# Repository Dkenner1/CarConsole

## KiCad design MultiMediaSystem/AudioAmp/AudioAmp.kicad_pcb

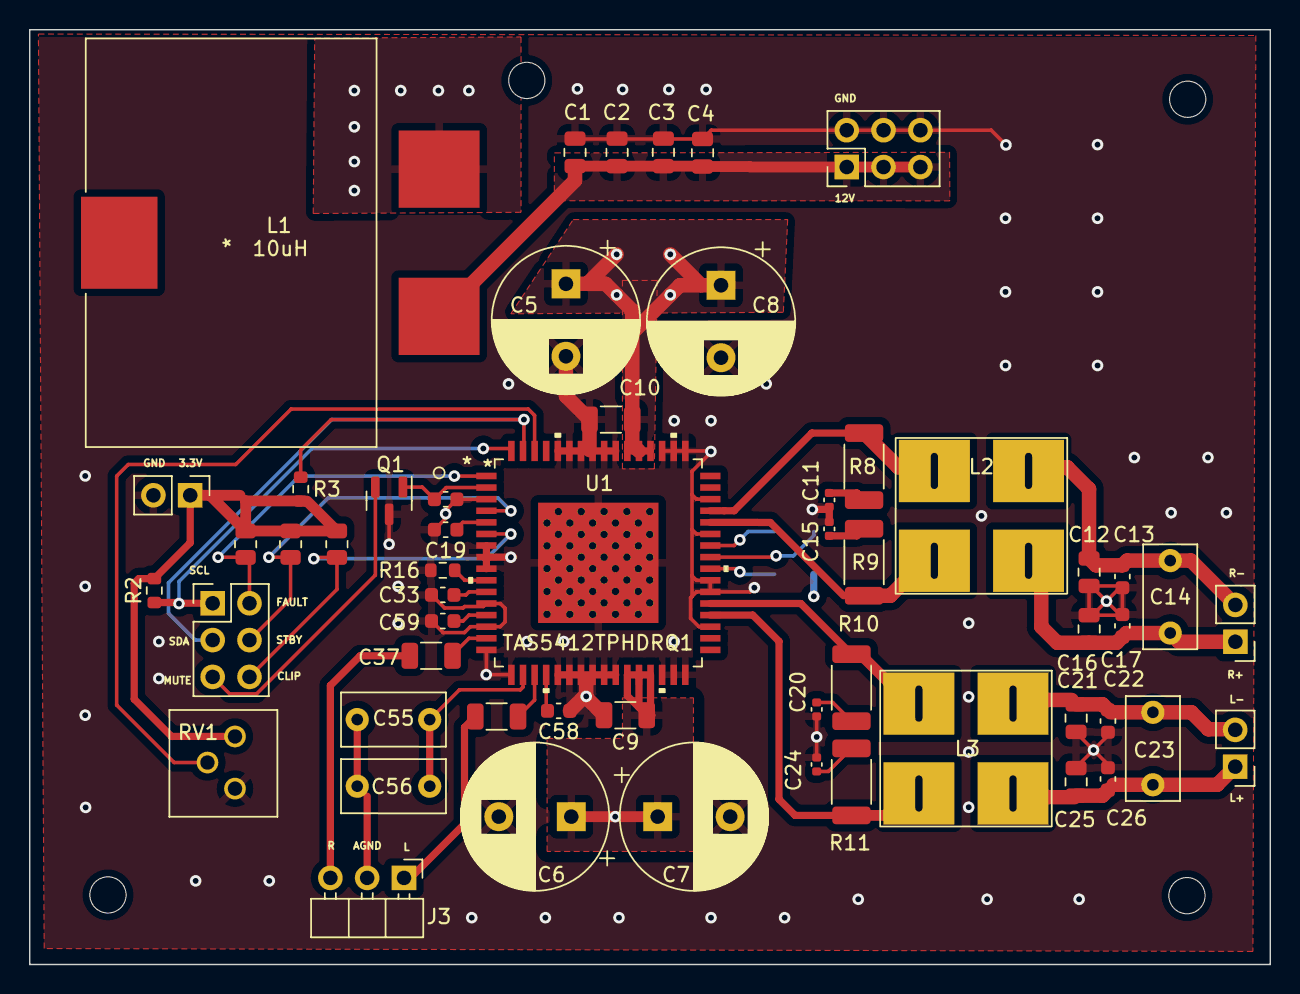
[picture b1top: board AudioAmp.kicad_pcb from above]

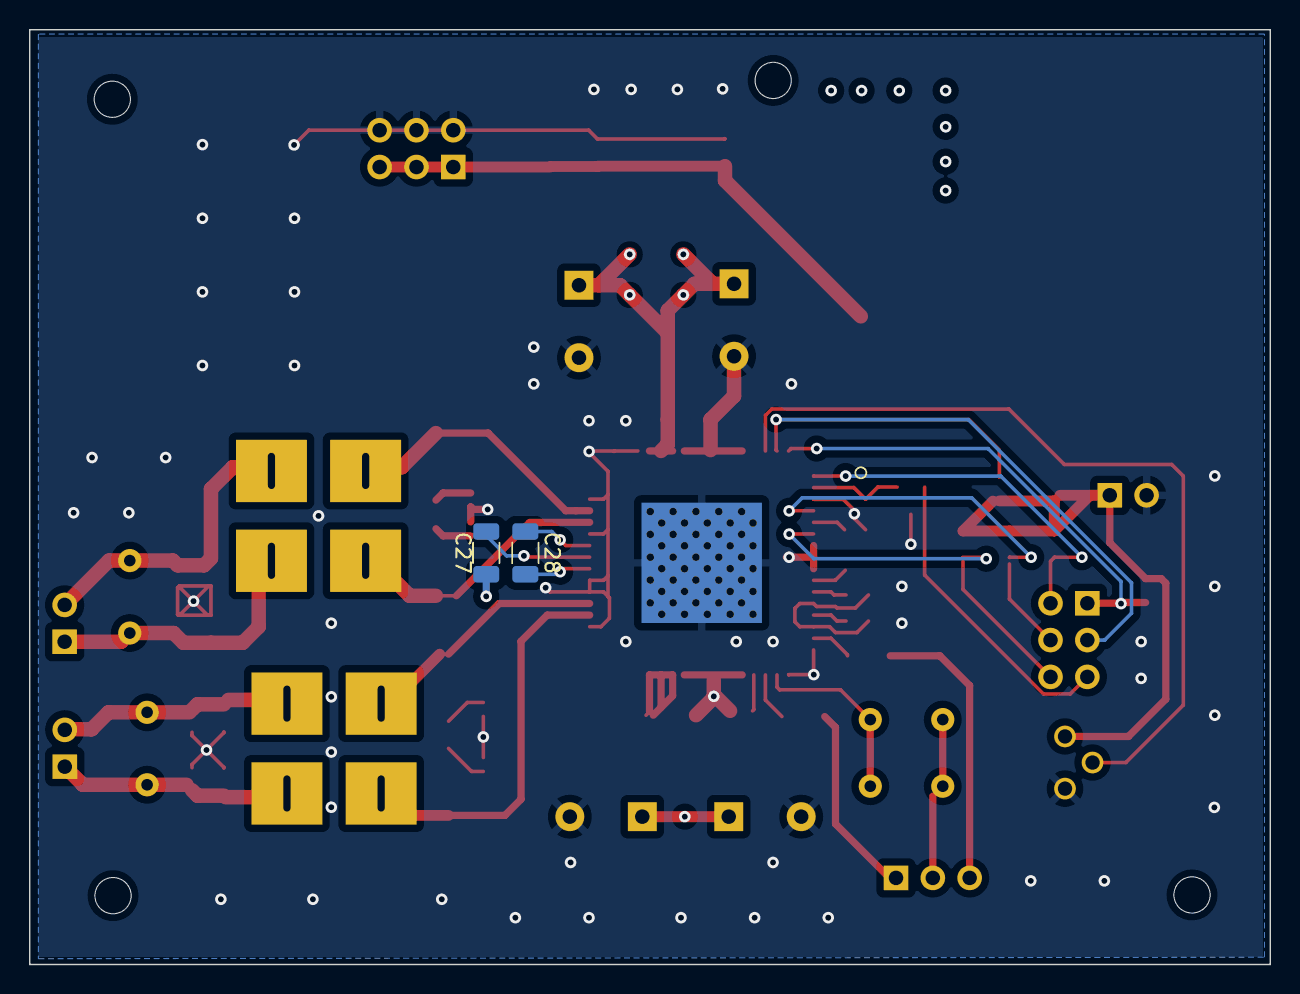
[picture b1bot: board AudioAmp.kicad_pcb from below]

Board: 4 copper layers, 85.6 x 64.5 mm, 61 parts (2 on the bottom side), 38 nets.

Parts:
C1, C2: 4.7uF; C_0805_2012Metric
C3: 82nF; C_0805_2012Metric
C4: 2.2nF; C_0805_2012Metric
C5, C6, C7, C8: 330uF; CP_Radial_D10.0mm_P5.00mm
C9, C10, C27, C28: 1uF; C_1206_3216Metric
C11, C15, C20, C24: 1nF; C_0402_1005Metric
C12, C16, C21, C25: 470nF; C_0805_2012Metric
C13, C17, C22, C26: 10nF; C_0603_1608Metric
C14, C23, C55, C56: .47uF; C_Rect_L7.0mm_W3.5mm_P5.00mm
C18: 220nF; C_0603_1608Metric
C19, C33, C58, C59: 100nF; C_0603_1608Metric
C37, C39: .47uF; C_1206_3216Metric
H1, H2, H3, H4: MountingHole; MountingHole_2.5mm
J1: Ctrl_pins; PinHeader_2x03_P2.54mm_Vertical
J2: PWR; PinHeader_2x03_P2.54mm_Vertical
J3: AudioIn; PinHeader_1x03_P2.54mm_Horizontal
J4: PULLUP_SRC; PinHeader_1x02_P2.54mm_Vertical
J5: Rspkr_o; PinHeader_1x02_P2.54mm_Vertical
J6: Lspkr_o; PinHeader_1x02_P2.54mm_Vertical
L1: 10uH; SER2918H-103KL
L2, L3: 10uH; JA4575-AL
Q1: q; SOT-23
R2, R3: 4.7K; R_0603_1608Metric
R5, R6, R7: 49.9K; R_0805_2012Metric
R8, R9, R10, R11: 5.6; R_2010_5025Metric
R16: 20k; R_0603_1608Metric
RV1: 50K pot; CT-6EW
U1: TAS5412TPHDRQ1

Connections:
+3V3: J4.1, R2.2, R3.2, R5.2, R6.2, R7.2, RV1.1
+12V: C1.1, C2.1, C3.1, C4.1, J2.1, J2.3, J2.5, L1.1
AudioGND: C55.1, C56.1, J3.2
CLIP_OTW: J1.6, R7.1, U1.6 (*CLIP_OTW)
CP: C27.2, U1.41 (CP)
CPC_TOP: C28.1, U1.42 (CPC_TOP)
CP_BOT: C28.2, U1.40 (CP_BOT)
FAULT: J1.2, R5.1, U1.1 (*FAULT)
GND: C1.2, C2.2, C3.2, C4.2, C5.2, C6.2, C7.2, C8.2, C9.2, C10.2, C11.1, C12.1, C13.1, C15.2, C16.2, C17.2, C18.2, C19.2, C20.1, C21.1, C22.1, C24.2, C25.2, C26.2, C33.2, C58.1, C59.2, J2.2, J2.4, J2.6, J4.2, Q1.3 (S), R16.1, RV1.3, U1.3 (GND), U1.7 (GND), U1.8 (GND), U1.9 (GND), U1.12 (GND), U1.14 (GND), U1.16 (GND), U1.17 (GND), U1.21 (GND), U1.22 (GND), U1.23 (GND), U1.24 (GND), U1.25 (GND), U1.26 (GND), U1.30 (GND), U1.31 (GND), U1.32 (GND), U1.35 (GND), U1.38 (GND), U1.39 (GND), U1.43 (GND), U1.46 (GND), U1.49 (GND), U1.50 (GND), U1.51 (GND), U1.55 (GND), U1.56 (GND), U1.57 (GND), U1.58 (GND), U1.59 (GND), U1.60 (GND), U1.EPAD
I2C_ADDR: RV1.2, U1.62 (I2C_ADDR)
IN1_P: C37.2, U1.15 (IN1_P)
IN2_P: C39.2, U1.19 (IN2_P)
IN_M: C55.2, C56.2, U1.18 (IN_M)
L: C39.1, J3.1
L_o+: C23.2, C25.1, C26.1, J6.1, L3.3
L_o-: C21.2, C22.2, C23.1, J6.2, L3.2
MUTE: J1.5, Q1.2 (G)
MUTE*: C18.1, Q1.1 (D), U1.2 (*MUTE)
unnamed: C11.2, R8.2
unnamed: C15.1, R9.1
unnamed: C19.1, U1.5 (D_BYP)
unnamed: C20.2, R10.2
unnamed: C24.1, R11.1
unnamed: C33.1, U1.11 (A_BYP)
unnamed: C58.2, U1.20 (CM_CAP2)
unnamed: C59.1, U1.13 (CM_CAP1)
unnamed: R16.2, U1.10 (REXT)
OUT1_M: L2.1, R8.1, U1.45 (OUT1_M)
OUT1_P: L2.4, R9.2, U1.44 (OUT1_P)
OUT2_M: L3.1, R10.1, U1.37 (OUT2_M)
OUT2_P: L3.4, R11.2, U1.36 (OUT2_P)
PVDD: C5.1, C6.1, C7.1, C8.1, C9.1, C10.1, C27.1, L1.2, U1.27 (PVDD), U1.28 (PVDD), U1.29 (PVDD), U1.52 (PVDD), U1.53 (PVDD), U1.54 (PVDD)
R: C37.1, J3.3
R_o+: C14.2, C16.1, C17.1, J5.1, L2.3
R_o-: C12.2, C13.2, C14.1, J5.2, L2.2
SCL: J1.1, R2.1, U1.64 (SCL)
SDA: J1.3, R3.1, U1.63 (SDA)
STANDBY: J1.4, R6.1, U1.4 (*STANDBY)

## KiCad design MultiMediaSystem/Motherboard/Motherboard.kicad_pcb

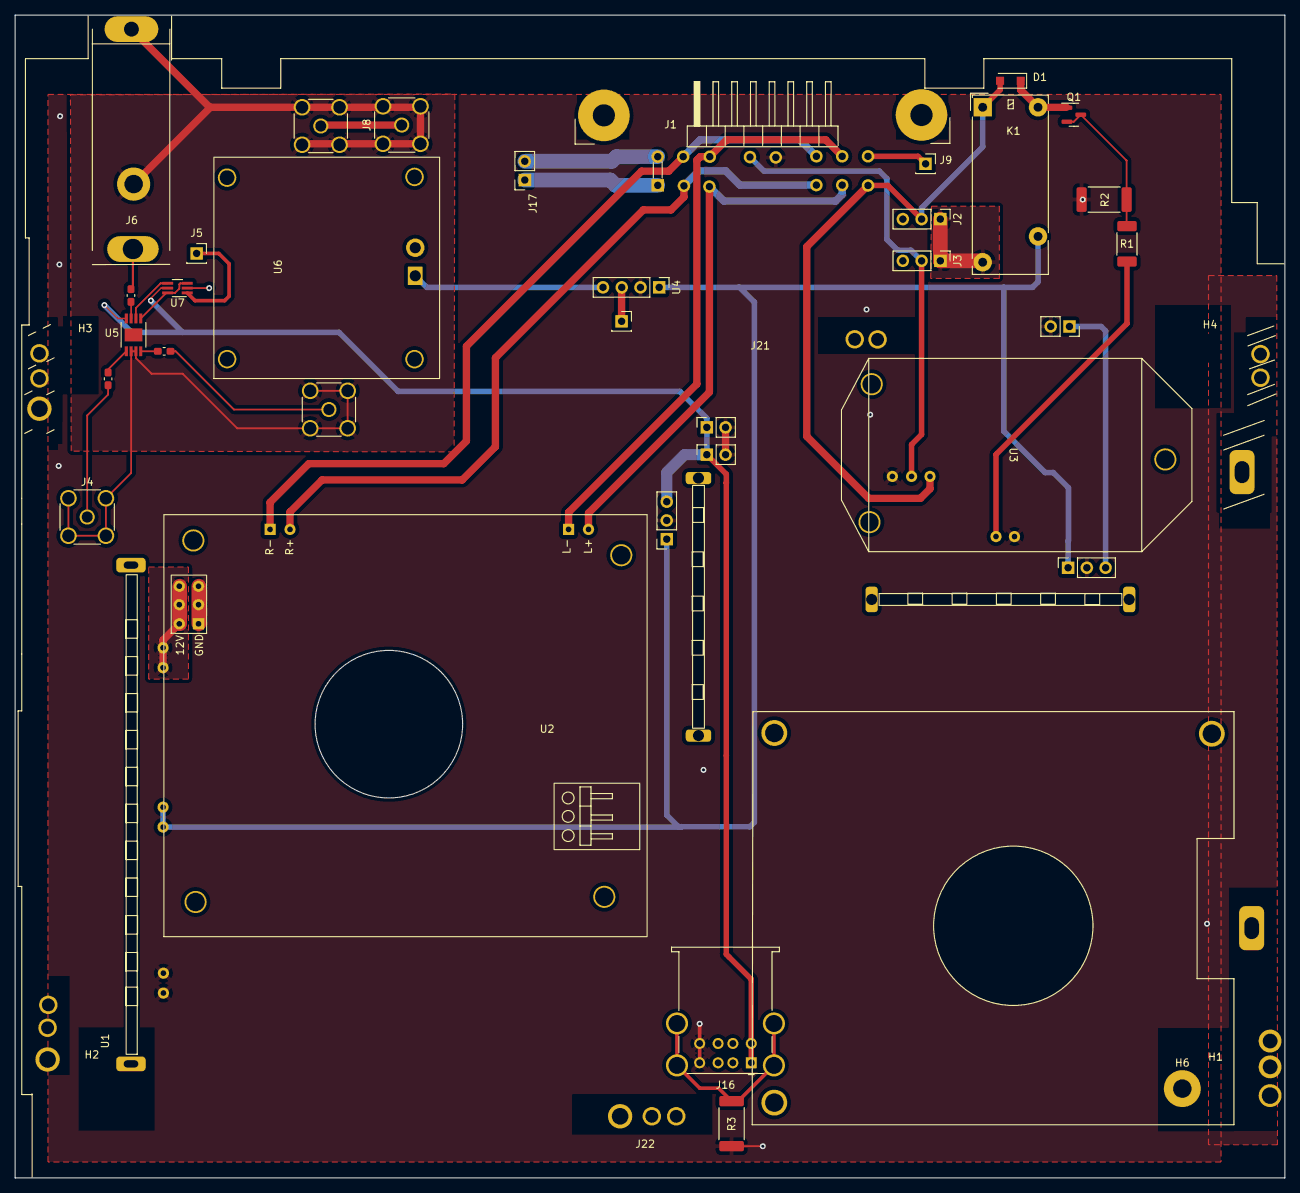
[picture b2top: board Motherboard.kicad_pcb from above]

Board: 2 copper layers, 172.1 x 157.6 mm, 42 parts (0 on the bottom side), 32 nets.

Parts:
C1, C2, C3: 10uF; C_0603_1608Metric_Pad1.08x0.95mm_HandSolder
D1: FS1B; D_SOD-123F
H1, H2, H3, H4: MountingHole; RectangleSlot
H5, H6, H7, H8: DAC_mount; MountingHole_2.5mm_Pad
J1: Wire Harness; HeadUnit_Conn
J2: Vmem Jumper; PinHeader_1x03_P2.54mm_Vertical
J3: Vacc_jumper; PinHeader_1x03_P2.54mm_Vertical
J4: RF_RX; SMA_Amphenol_132134_Vertical
J5: RF_CTRL; PinSocket_1x01_P2.54mm_Vertical
J6: AntennaExternal; SubaruRadioJack
J8: RF_TX; SMA_Amphenol_132134_Vertical
J9: AntennaPwr_Conn; PinSocket_1x01_P2.54mm_Vertical
J10: RF_EN; PinSocket_1x01_P2.54mm_Vertical
J14: 5V_1; PinSocket_1x02_P2.54mm_Vertical
J15: RPI_Buck; 5V_Reg_Footprint_VertMnt
J16: AUSB2-4599; USB_A_Wuerth_61400826021_Horizontal_Stacked
J17: Illum/Dim; PinSocket_1x02_P2.54mm_Vertical
J18: 5V_2; PinSocket_1x02_P2.54mm_Vertical
J19: GP_Buck; 5V_Reg_Footprint_VertMnt
J20: 5V_3; PinSocket_1x02_P2.54mm_Vertical
J21: Motherboard bracket; MotherBoard_Bracket_2
J22: Motherboard bracket; MotherBoard_Bracket_1
K1: ADW1112HTW; Relay_1P1T_NO_10x24x18.8mm_Panasonic_ADW11xxxxW_THT
Q1: T2N7002BK,LM; SOT-23
R1: RMCP2010FT470R; R_2010_5025Metric_Pad1.40x2.65mm_HandSolder
R2: RC2512JK-0747KL; R_2512_6332Metric_Pad1.40x3.35mm_HandSolder
R3: HCJ2512ZT0R00; R_2512_6332Metric_Pad1.40x3.35mm_HandSolder
U1: AudioAmp_PS
U2: AudioAmp
U3: PowerSupplyCtrl; PS_Controller
U4: RadioRegulator; PinHeader_1x04_P2.54mm_Vertical
U5: HMC784AMS8GETR
U6: RadioAmp
U7: SN74LVC2G06QDCKRQ1; SOT-363_SC-70-6_Handsoldering

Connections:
5V: J14.1, J15.3
5V_GP: J16.1 (VBUS1), J16.5 (VBUS2), J18.1, J19.3, J20.1, U5.4 (VDD), U7.5 (VCC)
8V: U4.4 (Vradio), U6.1 (Vsrc)
Antenna: C1.1, J6.1 (In)
Antenna_Pwr: J1.14, J9.1
AudioPwr: U1.3 (Vout), U2.1 (12V)
Dim: J1.7, J17.2
FrontSpkr_L+: J1.3, J1.5, U2.5 (L+)
FrontSpkr_L-: J1.9, J1.13, U2.6 (L-)
FrontSpkr_R+: J1.2, J1.4, U2.3 (R+)
FrontSpkr_R-: J1.8, J1.12, U2.4 (R-)
GND: J1.11, J14.2, J15.2, J16.4 (GND1), J16.8 (GND2), J18.2, J19.2, J20.2, R2.1, R3.1, U1.2 (GND), U2.2 (GND), U3.3 (GND), U4.2 (GND), U6.2 (GND), U7.2 (GND)
Illum: J1.1, J17.1
unnamed: C1.2, U5.3 (RFC)
unnamed: C2.1, U5.5 (RF1)
unnamed: C3.1, U5.8 (RF2)
unnamed: D1.1 (K), K1.6, Q1.1 (D)
unnamed: J16.9 (Shield), R3.2
unnamed: Q1.2 (G), Q1.3 (S), R1.2, R2.2
RELAY: R1.1, U3.6 (SWITCH)
RF_A: U5.1 (A), U7.3 (2A), U7.6 (1Y)
RF_ATX: C3.2, U6.5 (out)
RF_B: U5.2 (B), U7.4 (2Y)
RF_CTL: J5.1, U7.1 (1A)
RF_RX: C2.2, J4.1 (In)
RF_TX: J8.1 (In), U6.3 (in)
RF_gnd: J4.2 (Ext), J6.2 (Ext), J8.2 (Ext), U5.6 (GND), U5.7 (GND), U6.4 (in_gnd), U6.6 (out_gnd)
Radio_EN: J10.1, U4.3 (EN)
Vacc: J1.10, J3.2, U3.2 (Vmes)
Vdd: J2.1, J3.1, K1.3
Vmem: D1.2 (A), J1.6, J2.2, K1.1, U3.1 (Vin)
Vsrc: J15.1, J19.1, K1.5, U1.1 (Vin), U4.1 (Vsrc)

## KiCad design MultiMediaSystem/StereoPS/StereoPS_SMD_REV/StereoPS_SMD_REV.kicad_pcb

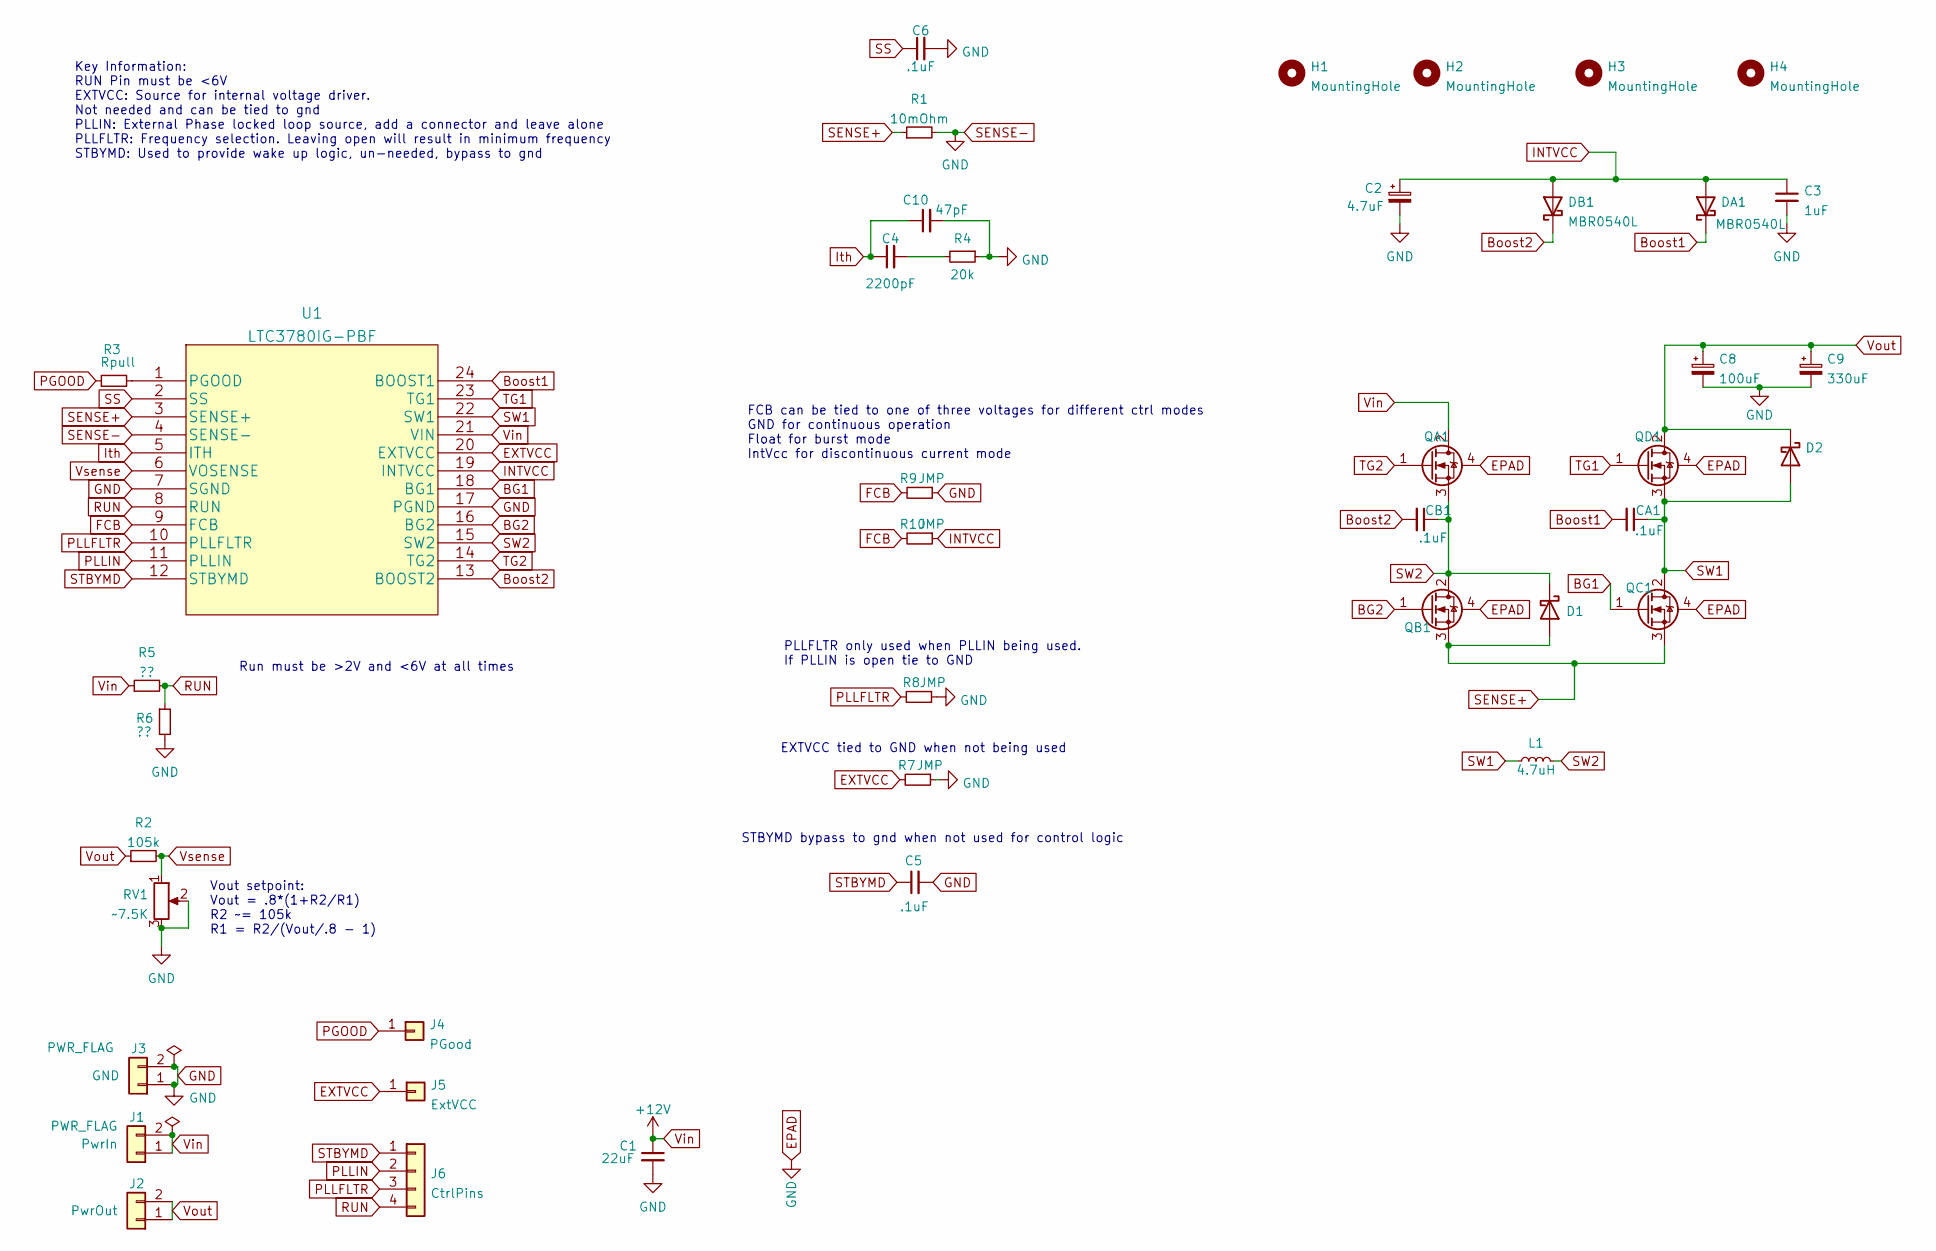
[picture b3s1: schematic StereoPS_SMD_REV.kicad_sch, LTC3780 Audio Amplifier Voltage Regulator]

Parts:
C1: 22uF; C_1206_3216Metric_Pad1.33x1.80mm_HandSolder
C2: 4.7uF; C_0805_2012Metric_Pad1.18x1.45mm_HandSolder
C3: 1uF; C_1206_3216Metric_Pad1.33x1.80mm_HandSolder
C4: 2200pF; C_0805_2012Metric_Pad1.18x1.45mm_HandSolder
C5, C6: .1uF; C_0603_1608Metric_Pad1.08x0.95mm_HandSolder
C8: 100uF; CP_Radial_D8.0mm_P3.50mm
C9: 330uF; CP_Radial_D10.0mm_P5.00mm
C10: 47pF; C_0603_1608Metric_Pad1.08x0.95mm_HandSolder
CA1: .1uF; C_0603_1608Metric_Pad1.08x0.95mm_HandSolder
CB1: .1uF; C_0603_1608Metric_Pad1.08x0.95mm_HandSolder
D1: SS34-E3; D_SOD-123
D2: SS32-E3; D_SOD-123
DA1: MBR0540L; D_SOD-123
DB1: MBR0540L; D_SOD-123
H1, H2, H3, H4: MountingHole; MountingHole_2.5mm
J1: PwrIn; PinHeader_1x02_P2.54mm_Horizontal
J2: PwrOut; PinHeader_1x02_P2.54mm_Horizontal
J3: GND; PinHeader_1x02_P2.54mm_Horizontal
J4: PGood; PinSocket_1x01_P2.54mm_Vertical
J5: ExtVCC; PinSocket_1x01_P2.54mm_Vertical
J6: CtrlPins; PinSocket_1x04_P2.54mm_Vertical
L1: 4.7uH; L_12x12mm_H8mm
QA1: RX3G07CGNC16; MSOP-8-1EP_3x3mm_P0.65mm_EP1.73x1.85mm
QB1: RX3G07CGNC16; MSOP-8-1EP_3x3mm_P0.65mm_EP1.73x1.85mm
QC1: RX3G07CGNC16; MSOP-8-1EP_3x3mm_P0.65mm_EP1.73x1.85mm
QD1: RX3G07CGNC16; MSOP-8-1EP_3x3mm_P0.65mm_EP1.73x1.85mm
R1: 10mOhm; R_0402_1005Metric_Pad0.72x0.64mm_HandSolder
R2: 105k; R_1206_3216Metric_Pad1.30x1.75mm_HandSolder
R3: Rpull; R_0805_2012Metric_Pad1.20x1.40mm_HandSolder
R4: 20k; R_1206_3216Metric_Pad1.30x1.75mm_HandSolder
R5, R6: ??; R_0805_2012Metric_Pad1.20x1.40mm_HandSolder
R7, R8, R9, R10: JMP; R_0805_2012Metric_Pad1.20x1.40mm_HandSolder
RV1: ~7.5K; CT-6EW
U1: LTC3780IG-PBF

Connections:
BG1: QC1.1 (G), U1.18 (BG1)
BG2: QB1.1 (G), U1.16 (BG2)
Boost1: CA1.2, DA1.1 (K), U1.24 (BOOST1)
Boost2: CB1.2, DB1.1 (K), U1.13 (BOOST2)
EPAD: C1.2, C2.2, C3.2, C5.2, C6.2, C8.2, C9.2, C10.2, J3.1, J3.2, QA1.4 (EPAD), QB1.4 (EPAD), QC1.4 (EPAD), QD1.4 (EPAD), R1.2, R4.1, R6.2, R7.1, R8.1, R9.1, RV1.2, RV1.3, U1.4 (SENSE-), U1.7 (SGND), U1.17 (PGND)
EXTVCC: J5.1, R7.2, U1.20 (EXTVCC); also elsewhere on the board
FCB: R9.2, R10.2, U1.9 (FCB)
INTVCC: C2.1, C3.1, DA1.2 (A), DB1.2 (A), R10.1, U1.19 (INTVCC)
Ith: C4.1, C10.1, U1.5 (ITH)
unnamed: C4.2, R4.2
unnamed: R3.2, U1.1 (PGOOD)
PGOOD: J4.1, R3.1
PLLFLTR: J6.3, R8.2, U1.10 (PLLFLTR)
PLLIN: J6.2, U1.11 (PLLIN)
RUN: J6.4, R5.2, R6.1, U1.8 (RUN)
SENSE+: D1.2 (A), QB1.3 (S), QC1.3 (S), R1.1, U1.3 (SENSE+)
SS: C6.1, U1.2 (SS)
STBYMD: C5.1, J6.1, U1.12 (STBYMD)
SW1: CA1.1, D2.2 (A), L1.1, QC1.2 (D), QD1.3 (S), U1.22 (SW1)
SW2: CB1.1, D1.1 (K), L1.2, QA1.3 (S), QB1.2 (D), U1.15 (SW2)
TG1: QD1.1 (G), U1.23 (TG1)
TG2: QA1.1 (G), U1.14 (TG2)
Vin: C1.1, J1.1, J1.2, QA1.2 (D), R5.1, U1.21 (VIN)
Vout: C8.1, C9.1, D2.1 (K), J2.1, J2.2, QD1.2 (D), R2.1
Vsense: R2.2, RV1.1, U1.6 (VOSENSE)

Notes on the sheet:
Key Information: RUN Pin must be <6V EXTVCC: Source for internal voltage driver. Not needed and can be tied to gnd PLLIN: External Phase locked loop source, add a connector and leave alone PLLFLTR: Frequency selection. Leaving open will result in minimum frequency STBYMD: Used to provide wake up lo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
EXTVCC tied to GND when not being used
Run must be >2V and <6V at all times
FCB can be tied to one of three voltages for different ctrl modes GND for continuous operation Float for burst mode IntVcc for discontinuous current mode
Vout setpoint: Vout = .8*(1+R2/R1) R2 ~= 105k R1 = R2/(Vout/.8 - 1)
PLLFLTR only used when PLLIN being used. If PLLIN is open tie to GND
STBYMD bypass to gnd when not used for control logic

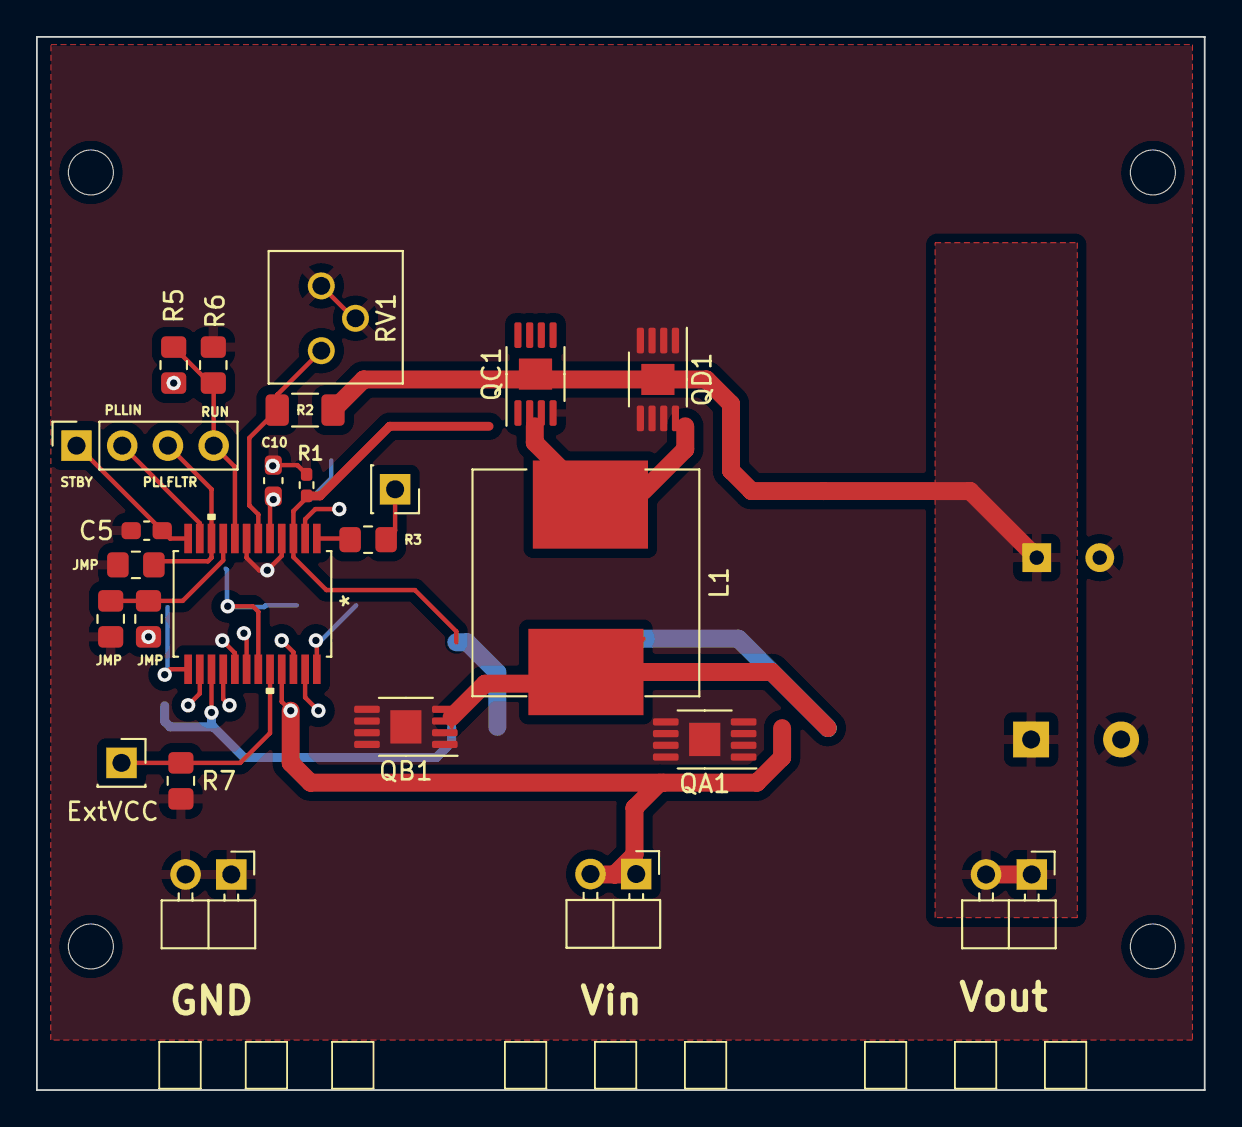
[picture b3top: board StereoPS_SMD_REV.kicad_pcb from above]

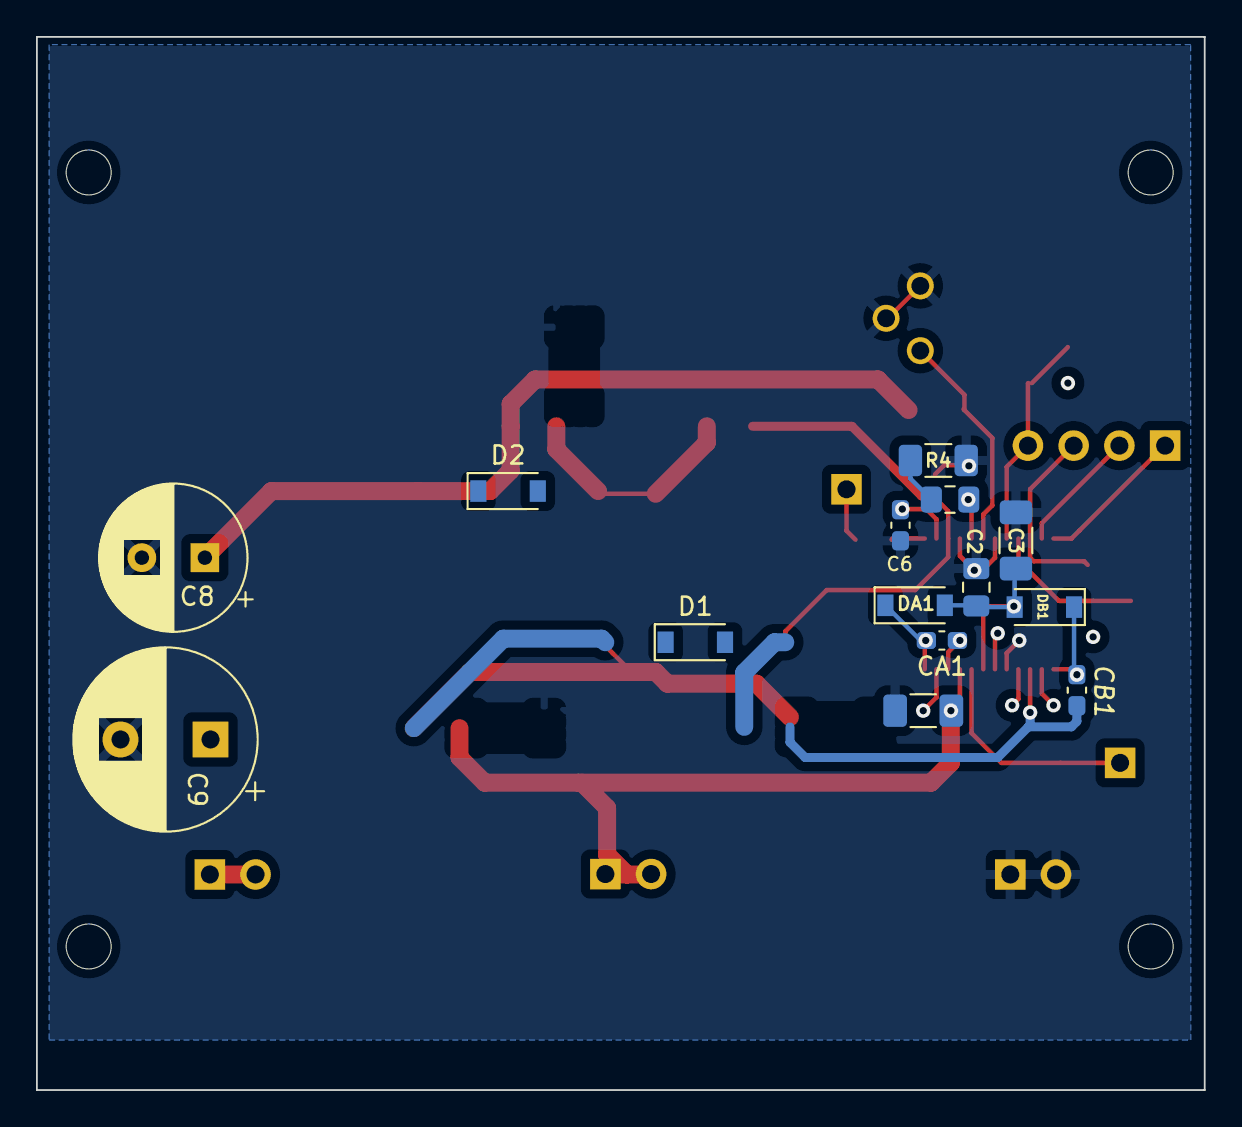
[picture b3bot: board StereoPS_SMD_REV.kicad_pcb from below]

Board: 4 copper layers, 64.9 x 58.5 mm, 42 parts (14 on the bottom side), 25 nets.

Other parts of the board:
ExtVCC: ExtVCC; PinSocket_1x01_P2.54mm_Vertical

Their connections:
EXTVCC: ExtVCC.1; also elsewhere on the board

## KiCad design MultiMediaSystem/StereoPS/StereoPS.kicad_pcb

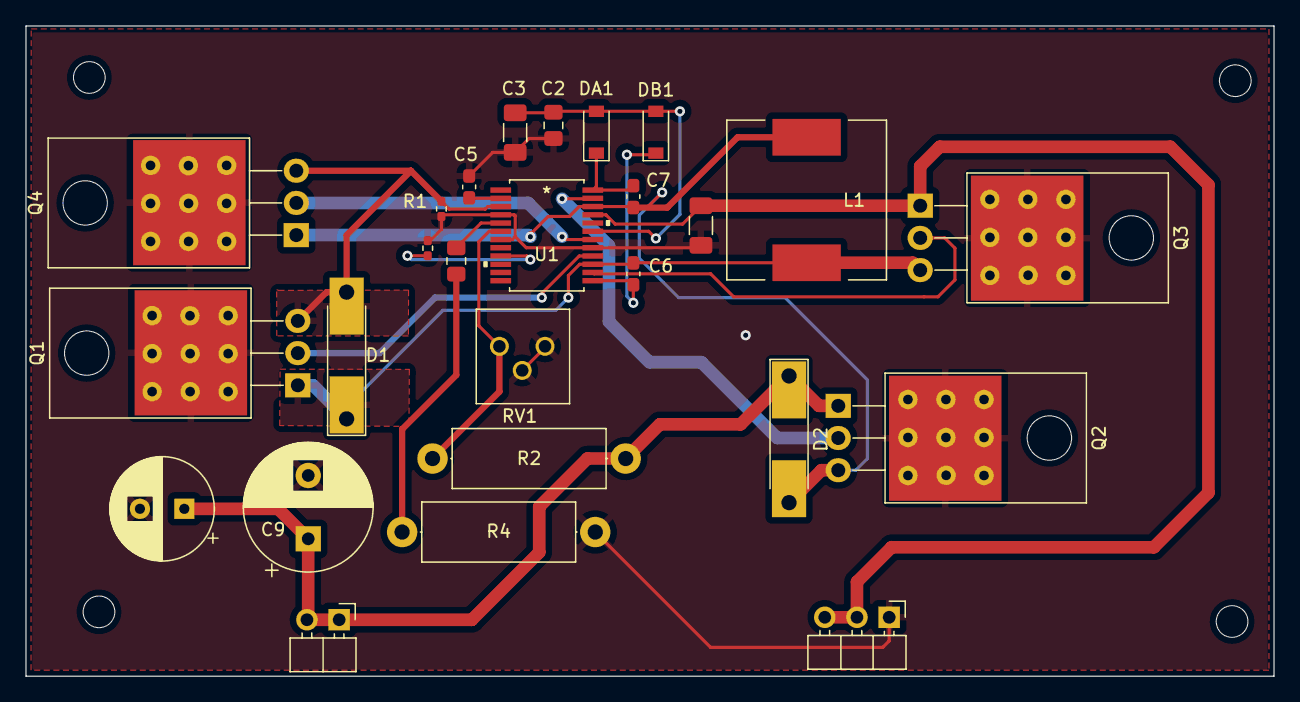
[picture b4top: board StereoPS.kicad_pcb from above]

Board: 2 copper layers, 98.5 x 51.3 mm, 30 parts (0 on the bottom side), 18 nets.

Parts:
C1: 22uF; C_1206_3216Metric_Pad1.33x1.80mm_HandSolder
C2: 4.7uF; C_0805_2012Metric_Pad1.18x1.45mm_HandSolder
C3: 1uF; C_1206_3216Metric_Pad1.33x1.80mm_HandSolder
C4: 2200pF; C_0805_2012Metric_Pad1.18x1.45mm_HandSolder
C5, C6, C7: .1uF; C_0603_1608Metric_Pad1.08x0.95mm_HandSolder
C8: 100uF; CP_Radial_D8.0mm_P3.50mm
C9: 330uF; CP_Radial_D10.0mm_P5.00mm
D1: SS34-E3; D_MELF-RM10_Universal_Handsoldering
D2: SS32-E3; D_MELF-RM10_Universal_Handsoldering
DA1: MBR0540L; D_SOD-123
DB1: MBR0540L; D_SOD-123
H1, H2, H3, H4: MountingHole; MountingHole_2.5mm
J1: PwrIn; PinHeader_1x03_P2.54mm_Horizontal
J2: PwrOut; PinHeader_1x02_P2.54mm_Horizontal
L1: 4.7uH; L_12x12mm_H8mm
Q1, Q2, Q3, Q4: RX3G07CGNC16; TO-220-3_Horizontal_TabDown_Thermal
R1: 10mOhm; R_0402_1005Metric_Pad0.72x0.64mm_HandSolder
R2: 105k; R_Axial_DIN0414_L11.9mm_D4.5mm_P15.24mm_Horizontal
R3: 0Ohm; R_0402_1005Metric_Pad0.72x0.64mm_HandSolder
R4: 20k; R_Axial_DIN0414_L11.9mm_D4.5mm_P15.24mm_Horizontal
RV1: ~7.5K; CT-6EW
U1: LTC3780IG-PBF

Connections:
BG1: Q4.2 (G), U1.18 (BG1)
BG2: Q1.2 (G), U1.16 (BG2)
Boost1: C7.2, DA1.1 (K), U1.24 (BOOST1)
Boost2: C6.2, DB1.1 (K), U1.13 (BOOST2)
FCB: R3.2, U1.9 (FCB)
GND: C1.2, C2.2, C3.2, C5.2, C8.2, C9.2, J1.1, Q1.4 (EPAD), Q2.4 (EPAD), Q3.4 (EPAD), Q4.4 (EPAD), R1.2, R3.1, R4.1, RV1.2, RV1.3, U1.4 (SENSE-), U1.7 (SGND), U1.17 (PGND)
INTVCC: C2.1, C3.1, DA1.2 (A), DB1.2 (A), U1.19 (INTVCC)
Ith: C4.1, U1.5 (ITH)
unnamed: C4.2, R4.2
SENSE+: D1.2 (A), Q1.3 (S), Q4.3 (S), R1.1, U1.3 (SENSE+)
SS: C5.1, U1.2 (SS)
SW1: C7.1, D2.2 (A), L1.1, Q2.3 (S), Q4.1 (D), U1.22 (SW1)
SW2: C6.1, D1.1 (K), L1.2, Q1.1 (D), Q3.3 (S), U1.15 (SW2)
TG1: Q2.2 (G), U1.23 (TG1)
TG2: Q3.2 (G), U1.14 (TG2)
Vin: C1.1, J1.2, J1.3, Q3.1 (D), U1.21 (VIN)
Vout: C8.1, C9.1, D2.1 (K), J2.1, J2.2, Q2.1 (D), R2.2
Vsense: R2.1, RV1.1, U1.6 (VOSENSE)

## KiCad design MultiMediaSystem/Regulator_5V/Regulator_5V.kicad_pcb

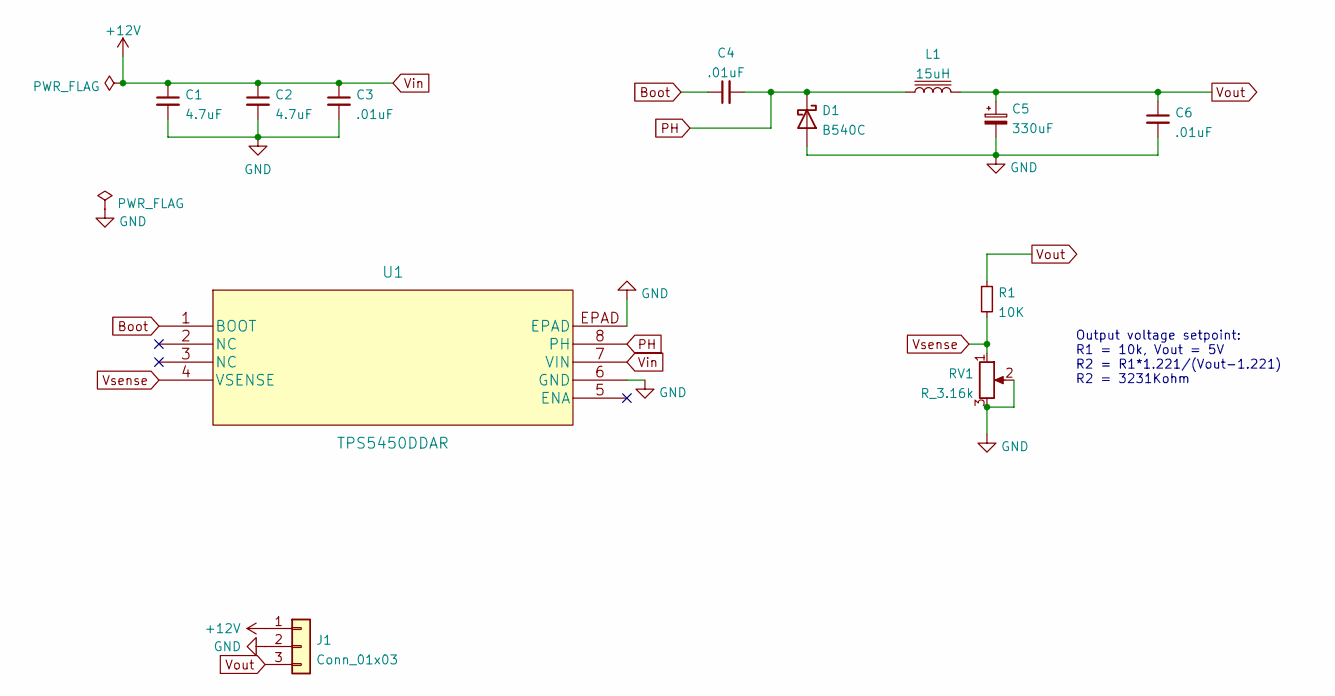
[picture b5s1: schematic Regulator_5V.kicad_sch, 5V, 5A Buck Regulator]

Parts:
C1, C2: 4.7uF; C_0805_2012Metric_Pad1.18x1.45mm_HandSolder
C3, C4, C6: .01uF; C_0603_1608Metric_Pad1.08x0.95mm_HandSolder
C5: 330uF; CP_EIA-7343-15_Kemet-W_Pad2.25x2.55mm_HandSolder
D1: B540C; D_MELF_Handsoldering
J1: Conn_01x03; PinHeader_1x03_P2.54mm_Horizontal
L1: 15uH; SER2918H-103KL
R1: 10K; R_0805_2012Metric_Pad1.20x1.40mm_HandSolder
RV1: R_3.16k; GF063P1
U1: TPS5450DDAR

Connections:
Boot: C4.1, U1.1 (BOOT)
GND: C1.2, C2.2, C3.2, C5.2, C6.2, D1.2 (A), J1.2, RV1.2, RV1.3, U1.6 (GND), U1.EPAD
PH: C4.2, D1.1 (K), L1.1, U1.8 (PH)
Vin: C1.1, C2.1, C3.1, J1.1, U1.7 (VIN)
Vout: C5.1, C6.1, J1.3, L1.2, R1.1
Vsense: R1.2, RV1.1, U1.4 (VSENSE)

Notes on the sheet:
Output voltage setpoint: R1 = 10k, Vout = 5V R2 = R1*1.221/(Vout-1.221) R2 = 3231Kohm

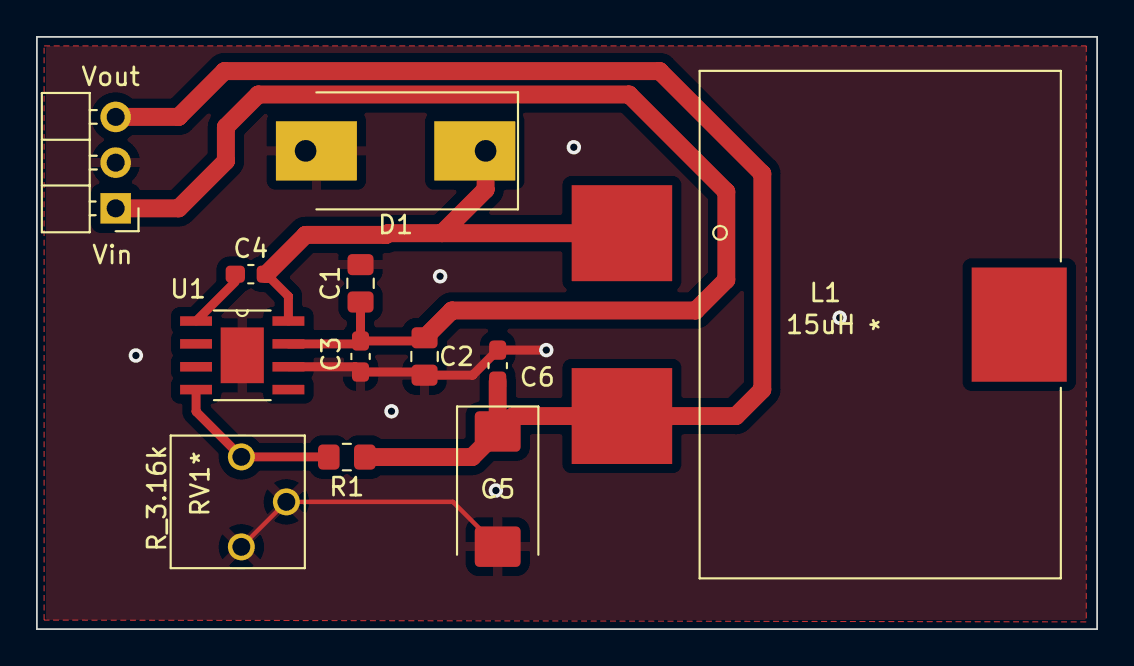
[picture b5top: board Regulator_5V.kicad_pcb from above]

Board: 2 copper layers, 58.9 x 32.9 mm, 12 parts (0 on the bottom side), 6 nets.

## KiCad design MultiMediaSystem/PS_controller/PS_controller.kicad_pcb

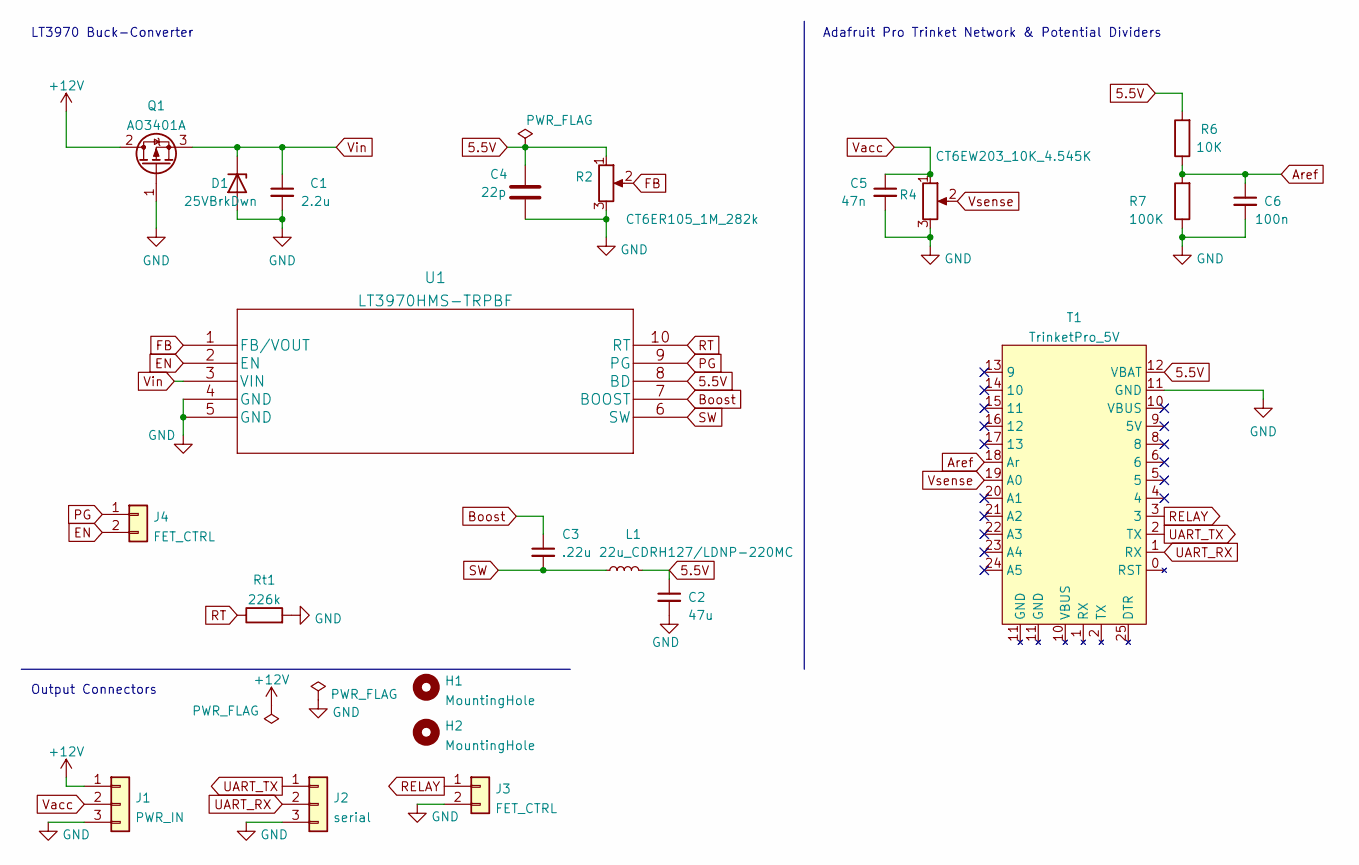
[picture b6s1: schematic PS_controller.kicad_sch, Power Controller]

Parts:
C1: 2.2u; C_0805_2012Metric_Pad1.18x1.45mm_HandSolder
C2: 47u; C_1206_3216Metric_Pad1.33x1.80mm_HandSolder
C3: .22u; C_0603_1608Metric_Pad1.08x0.95mm_HandSolder
C4: 22p; C_0805_2012Metric_Pad1.18x1.45mm_HandSolder
C5: 47n; C_0805_2012Metric_Pad1.18x1.45mm_HandSolder
C6: 100n; C_0.64x0.4_Handsolder
D1: 25VBrkDwn; D_SOD-123
H1, H2: MountingHole; MountingHole_2.5mm
J1: PWR_IN; PinSocket_1x03_P2.54mm_Vertical
J2: serial; PinSocket_1x03_P2.54mm_Vertical
J3, J4: FET_CTRL; PinSocket_1x02_P2.54mm_Vertical
L1: 22u_CDRH127/LDNP-220MC; L_12x12mm_H8mm
Q1: AO3401A; SOT-23
R2: CT6ER105_1M_282k; GF063P1
R4: CT6EW203_10K_4.545K; CT-6EW
R6: 10K; R_0603_1608Metric_Pad0.98x0.95mm_HandSolder
R7: 100K; R_1206_3216Metric_Pad1.30x1.75mm_HandSolder
Rt1: 226k; R_0402_1005Metric_Pad0.72x0.64mm_HandSolder
T1: TrinketPro_5V; TrinketPro5V
U1: LT3970HMS-TRPBF

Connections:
5.5V: C2.1, C4.1, L1.2, R2.1, R6.2, T1.12 (VBAT), U1.8 (BD)
+12V: J1.1, Q1.2 (D)
Aref: C6.1, R6.1, R7.2, T1.18 (Ar)
Boost: C3.1, U1.7 (BOOST)
EN: J4.2, U1.2 (EN)
FB: R2.2, U1.1 (FB/VOUT)
GND: C1.2, C2.2, C4.2, C5.2, C6.2, D1.2 (A), J1.3, J2.3, J3.2, Q1.1 (G), R2.3, R4.3, R7.1, Rt1.2, T1.11 (GND), U1.4 (GND), U1.5 (GND)
PG: J4.1, U1.9 (PG)
RELAY: J3.1, T1.3
RT: Rt1.1, U1.10 (RT)
SW: C3.2, L1.1, U1.6 (SW)
UART_RX: J2.2, T1.1 (RX)
UART_TX: J2.1, T1.2 (TX)
Vacc: C5.1, J1.2, R4.1
Vin: C1.1, D1.1 (K), Q1.3 (S), U1.3 (VIN)
Vsense: R4.2, T1.19 (A0)

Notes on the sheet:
Output Connectors
Adafruit Pro Trinket Network & Potential Dividers
LT3970 Buck-Converter

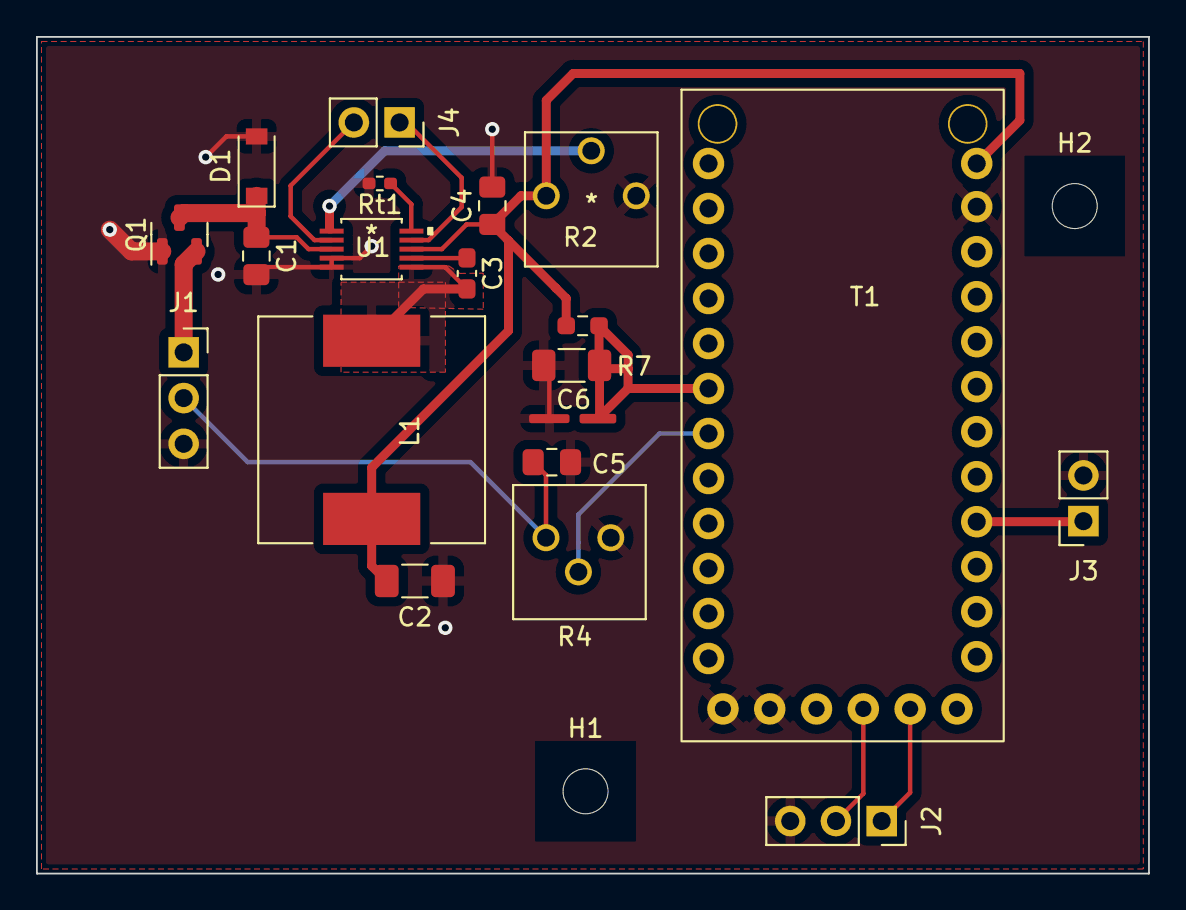
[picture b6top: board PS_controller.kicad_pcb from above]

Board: 2 copper layers, 61.8 x 46.5 mm, 22 parts (0 on the bottom side), 16 nets.

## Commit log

2022-04-29 Removed Extra Files
2022-05-05 Adjusted Motherboard Pinouts
    Motherboard pinout's were slightly off. This corrects that problem.
2022-10-20 Updated all designs

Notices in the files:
parts and their libraries:
Copyright 2021 Accelerated Designs. All rights reserved.
